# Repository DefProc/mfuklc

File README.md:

> Although the nerf range project was successful, it turned out that there was little interest in the competative building portion of this project. On the upside, the range had 5 installs during 2015, with hundreds of excited players during that time. 

> So although the MFUKLC project (it's a *terrible* acronym) has now reached it's conclusion, the same technology (with upgrades like full colour, animated, LED targets) lives on as [Made Invaders](https://github.com/DoESLiverpool/made-invaders).

> DefProc, 2016

# MFUKLC - Lasercut Challenge 
Your challenge, should you choose to accept it, is to build a device that can propel small light weight projectiles against a target. 

Round 1: MakerFaire UK 2015 (25-26 April Newcastle) [MakerFaire UK](http://www.makerfaireuk.com/). 

Round 2: MakeFest Liverpool 2015 (27th June, Central Library, Liverpool) [LpoolMakeFest](https://lpoolmakefest.wordpress.com).

Round 3: MakeFest Manchester 2015 (8–9th August, MOSI, Manchester) [MakeFest](http://www.mosi.org.uk/whats-on/makefest.aspx).

Round 4: Oggcamp '16

Take a look at the [rules](https://github.com/DefProc/mfuklc/tree/master/rules) to find out what you need to do. You can be a part of this challenge, either by entering at an event where the target will be, or by running your own event wherever and whenever you choose.

**Entries are now open to participate at Maker Faire UK 2015**

If you'd like to participate or have additional questions contact [@defproc](https://twitter.com/defproc) or [@MFUKLC](https://twitter.com/MFUKLC). Along with coming to [Maker Faire UK](http://www.makerfaireuk.com) in April 2015, we will also ask for:	

* your twitter name so we can add you to the [list of participants](https://twitter.com/MFUKLC/entrants),
* your github account name so we can give you write access to this repository,
* an email address would be nice in case we need to make any notifications,
* you be enthusiastic and open about your entry!
	
If you'd like to follow each teams progress and enjoy the trash talking follow the hash tag [ #MFUKLC](https://twitter.com/search?q=%23MFUKLC&src=typd) "**M**ega **F**un **U**nited **K**ingdom **L**aser **C**hallenge" or follow the twitter account [@MFUKLC](https://twitter.com/MFUKLC) to see @replies for the challenge in your timeline.
	
*Although this activity is running at the Maker Faire UK event, it is in no way affiliated with either Maker Faire UK or Make Media. It's an event being run by exhibitors* at *Maker Faire UK.*
	
## Repository Structure
	
 * [entries/](https://github.com/DefProc/mfuklc/tree/master/entries)
	* /AAAA/	subdirectories per entrant with 4-letter, upercase name,
 * [range/](https://github.com/DefProc/mfuklc/tree/master/range)	files for the range that will be used to score the entries,
 * [resources/](https://github.com/DefProc/mfuklc/tree/master/resources)	links, descriptions and resources to help participants, 
 * [rules/](https://github.com/DefProc/mfuklc/tree/master/rules)	the rules,
 * [trophy/](https://github.com/DefProc/mfuklc/tree/master/trophy)	files for the trophy.
	
## Short Link

Short link to this repository.

[defproc.co.uk/MFUKLC](http://defproc.co.uk/MFUKLC)

[oom.lt/MFUKLC](http://oom.lt/MFUKLC)

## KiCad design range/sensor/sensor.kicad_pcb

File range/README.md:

# Range

## Target

## Score Board  
   
The scoreboard is made using seven segment displays by [Matthew Venn](https://github.com/mattvenn/big-led-driver)

Files: MFUKLC-scoreboard-working.cdr (all other formats are generated (will switch to SVG once base design work done))

## Todo
* Sound -- Do we want a speaker or something more ecletic (fog horn)
* Target -- How many, what size/s how to house/hang

## Modules

### Control Module (CM)

The main control module.  

#### Microcontroller Pins (Arduino Mega)
* DIGITAL 13 -- Start Button -- (pin 13 so can connect other pin to ground with standard 2 pin header)

#### Connectors
* (U1) USB Type B -- For Arduino Connection
* (DC1) 2.1mm DC Jack -- For Power (12 v) 
* (BM) -- Button Module -- 2.1mm DC Jack -- N/O Switch
* (TM) -- Time Module -- 8 pin 2.54mm Dupont style connector 
* (SM) -- Score Module -- 8 pin 2.54mm Dupont style connector
* (RM) A-D -- Target modules -- To be determined.  

### Parts
* BOLT-M6-X-12-01 (x32) -- M6 x 12 mm Bolt
* NUTT-M6-M-STAN-01 (x32) -- M6 Nut
* CM-01 (x1) -- Base Plate
* CM-02 (x2) -- Side Plate
* CM-02-C (x1) -- Side Plate (Connections) Score Board
* CM-02-B (x1) -- Side Plate (Connections) Arduino (NOT YET DESIGNED)
* CM-03 (x1) -- Top (to be cut from acrylic)
* OOBB-MP-BREB-05-03 (x2) -- Breadboard Mounting Plate (5x3)
* OOBB-MP-ARDM-07-03 (x1)Arduino Mega Mounting Plate (7x3)
* OOBB-MP-I01-08-03-02 (A-D) (x2) -- Mounting Plate 8 pin 2.54 mm Connector

### Time Module (TM)

A 3 digit display to show the 30 second countdown
#### Connectors
* Only one (OE,LE,CLK,SDI,12V,5V,gnd) (gnd black)

#### Parts
* BOLT-M6-X-12-01 (x20) -- M6 x 12 mm Bolt
* NUTT-M6-M-STAN-01 (x20) -- M6 Nut
* NHFF-M3-X-30-01 (x12) -- M3 x 30 mm Nylon Standoff (F-F)
* NSCR-M3-X-12-70 (x24) -- M3 x 12 mm Nylon Screw Cross Head
* Matrix Module (x3) -- [Matrix Module](https://github.com/mattvenn/big-led-driver) -- By Matt Venn
* TM-01 (x1) -- Back -- Back, holds the matrices, and connector block
* TM-02 (x2) -- Side (Long) -- Long side piece.
* TM-03 (x1) -- Side (Short) -- Short side.
* TM-03-C (x1) -- Side (Short, Connections) -- Short Side with connections.
* TM-04 (x1) -- Top -- Top (to be cut from smoked acrylic)
* OOBB-MP-I01-08-03-02 (A-D) (x1) -- Mounting Plate 8 pin 2.54 mm Connector

### Score Module (SM)
A  6 digit display for showing the runs score.

#### Connectors
*    

#### Parts
* BOLT-M6-X-12-01 (x28) -- M6 x 12 mm Bolt
* NUTT-M6-M-STAN-01 (x28) -- M6 Nut
* NHFF-M3-X-30-01 (x12) -- M3 x 30 mm Nylon Standoff (F-F)
* NSCR-M3-X-12-70 (x24) -- M3 x 12 mm Nylon Screw Cross Head
* Matrix Module (x3) -- [Matrix Module](https://github.com/mattvenn/big-led-driver) -- By Matt Venn
* SM-01 (x1) -- Back -- Back, holds the matrices, and connector block
* SM-02 (x2) -- Side (Long) -- Long side piece.
* SM-03 (x1) -- Side (Short) -- Short side.
* SM-03-C (x1) -- Side (Short, Connections) -- Short Side with connections.
* SM-04 (x1) -- Top -- Top (to be cut from smoked acrylic)
* OOBB-MP-I01-08-03-02 (A-D) (x1) -- Mounting Plate 8 pin 2.54 mm Connector

### Target Module (RM) (x6) 

The targets

#### Connectors
* Only one 2.1mm barrel jack, center signal, outer gnd.

#### Parts
* BOLT-M6-X-12-01 (x8) -- M6 x 12 mm Bolt
* NUTT-M6-M-STAN-01 (x8) -- M6 Nut
* RM-01 (x1) -- Base -- The base that holds the PCB glued in place.
* RM-02 (x3) -- Side -- The side
* RM-02-C (x1) -- Side (Connections) -- The side with a hole for a 2.1mm barrel jack
* RM-03-2K (x1) -- Top (2000) -- The top (this one for 2000 points)

### Button Module (BM)

A 100 mm button to start the timing

#### Connectors
* Only one two pin button close (NO), 2.1mm DC jack.

#### Parts
* BOLT-M6-X-12-01 (x24) -- M6 x 12 mm Bolt
* NUTT-M6-M-STAN-01 (x24) -- M6 Nut
* ABUT-100-R-STAN-01 (x1) -- 100 mm Red Arcade Button
* DCJP-21D-X-08PM-01 (x1) -- 2.1 mm Panel Mount (8mm) DC Jack
* CRFM-48D-R-STAN-01 (x2) -- 4.8 mm Red Female Crimp Connector
* BM-01 (x1) -- Top -- Has a hole for a 100 mm button, is  173 mm x 173 mm (9x9 OOBB)
* BM-02 (x3) -- Side -- Side Panel 
* BM-02-C (x1) -- Side (Connections) -- Side Panel with conenctions
* BM-03 (x1) -- Bottom -- Bottom Panel173 mm x 173 mm (9x9 OOBB)
* BM-04 (x2) -- Base -- A base for the box to sit on, has holes to screw down or glue stars to glue.

## Bin Lid

Transporting amunition is an issue. We use a rubbish bin with a custom lid.

## Stencil

Branding is always important. To aid in this we have an A4 #MFUKLC stencil

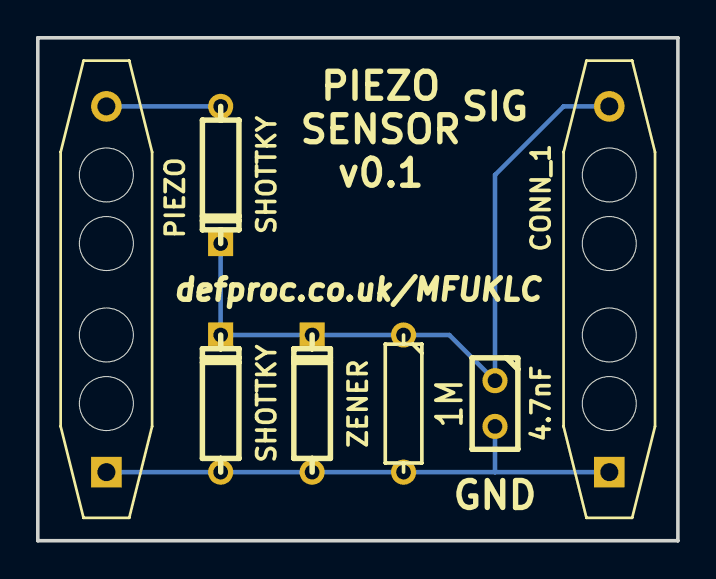
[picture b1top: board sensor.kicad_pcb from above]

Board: 2 copper layers, 35.6 x 27.9 mm, 7 parts (0 on the bottom side), 3 nets.

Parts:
4.7nF: 4.7nF; C1
CONN_1: CONN_2; PZ1
PIEZO: PIEZO; PZ1
R1: 1M; R3
SHOTTKY: SHOTTKY DIODE SR1100; D3
SHOTTKY#2: SHOTTKY DIODE SR1100; D3
ZENER: ZENER DIODE 1N751A; D3

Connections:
GND: 4.7nF.2, CONN_1.2, PIEZO.2, R1.2, SHOTTKY.1, ZENER.1
unnamed: PIEZO.1, SHOTTKY#2.1
SIGNAL: 4.7nF.1, CONN_1.1, R1.1, SHOTTKY.2, SHOTTKY#2.2, ZENER.2

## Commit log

2015-01-27 Initial Workings
    -File structure added
    -Main readme filled in
    -Added trophy files
    -Added Oomlout's entry file (no working yet)
2015-01-27 Added README.md's to empty folders
2015-01-27 revised licence file to allow individual entries their own terms
2015-01-27 moved the rules draft from google docs into markdown here
2015-01-27 Updated shortlink to point to this repository.
2015-01-27 Changed shortlink.
2015-01-28 Oomlout's Initial Workings
    Oomlout Changes
    - Pieces to cut to prototype a launcher
    - Notes added to readme (Inspiration, Proto Parts, Files Explained)
    - Generated file formats made
    Main Body Changes
    - Added link to hash tag to main readme.
2015-01-28 Fixed Markdown Formatting
2015-01-28 Re-Fixed MarkDown Formatting
2015-01-29 Some Design Working, Trophy Updating
2015-01-29 Fixing Image Link
2015-01-29 Changed Acronym to Mega Fun
2015-01-30 Added HobbyKing Second Round Sample Details
2015-01-30 Updated Design, and Trophy
2015-02-01 make sure it's clear that the MFUKLC project is not affiliated with the event
2015-02-02 Prototype one details.
2015-02-02 renamed root dirs to lowercase (because convention and cli typing!)
2015-02-02 removed backup file — because git!
2015-02-02 Doing a lot of housekeeping and not much designing #justSaying
2015-02-02 Launcher Refactoring
2015-02-02 added gitignore for kicad files
2015-02-02 first pass at the sensor schematic
2015-02-02 at least someone's doing the tidying up!
2015-02-03 updates to resources for ball and dart pricing
2015-02-03 Slight Change to design
2015-02-03 Design Changing
2015-02-04 Added Speed spreadsheet, and more HobbyKing Stuff
2015-02-05 Fixed folder capitalization issue.
2015-02-05 Motor mounts for new design. Updated Design notes.
2015-02-05 Updated Design Notes
2015-02-05 Fixed Markup, Added image resolutions
2015-02-05 Tidied up MarkUp
2015-02-05 Formatted README Entry page.
2015-02-05 Final Current Readme Updates
2015-02-05 Added Youtube video for motor balancing.
2015-02-05 Fixed Up Pieces for Prototype 3
2015-02-05 Added Scoreboard Working, generated images.
2015-02-05 Fixed Scoreboard Image
2015-02-05 Changed Scoreboard Image Size
2015-02-05 Generated formats for viewing/sharing.
2015-02-06 Added T-Joint to Vacuum Design
2015-02-06 moved to entries — I think this is where you meant
2015-02-06 added @MFUKLC twitter account and corrected folder names
2015-02-06 Added version one files and images
    Also contains failure and improvement write up
2015-02-06 Improvements list added for V1
2015-02-06 housekeeping: moved PIMO to entries/
2015-02-06 added some design notes to the DEFP entry
2015-02-06 confirmation that we'll be at maker faire and the call for entries
2015-02-07 Moved and updated Vacuum Testing
2015-02-07 Split Entries OOML & OOMV
2015-02-07 Added Directory to Entries Readme
2015-02-07 Fixed Markdown issues (discovered preview mode so hopefully fewer edits from me)
2015-02-07 Fixed Pimoroni Web Address
2015-02-07 Generated Files
2015-02-07 Moved Resources from ammunition.mkdn to README.md (added OOML sources)
2015-02-07 Fixed List Format
2015-02-07 Added additional amazon source
2015-02-07 Worked on designs.
2015-02-07 Added todo notes. Drew new vacuum nozzle
2015-02-08 Generated Formats.
2015-02-08 had a go at creating a piezo board and gerbers
2015-02-10 Updated Design, Removed video files from
2015-02-10 Updated Design documenting
2015-02-10 Fixed current entry image.
2015-02-10 updated the main README to include links
2015-02-10 added svg ammunition templates to resources
2015-02-10 Updated design (worked on ball chain and ball feeder)
2015-02-11 new defproc.co.uk/MFUKLC short link
2015-02-12 Worked on design a bit.
2015-02-12 Removed old files from git repo.
2015-02-12 Worked on design
2015-02-17 Version 2 first commit
2015-02-20 Updated Design.
    Added Prototype 4 to README
    Added Additional Hobby King test Components
    Added Images of P4 and control.
2015-02-25 Updated Entry Details.
2015-02-25 Worked on scoreboard.
2015-02-26 Some scoreboard changes.
2015-02-26 Added Score Board Images
2015-02-26 Added Resolutions
2015-02-26 Updated Scoreboard Readme With Images
2015-02-27 Added Score Module
2015-03-04 Started working on cleaning up.
2015-03-05 Worked on drive wheel.
2015-03-08 Updated Scoreboard
2015-03-09 added cardboard box range components
2015-03-09 Worked on Making Design Cleaner
2015-03-15 revised sensor board, and removed previous gerbers
2015-03-15 added rev.2 gerbers
2015-03-24 added code for serial controlled, 30 second, 8 segment LED countdown display
2015-03-24 new, basic piezo sensor tester using INT0 and LED_BUILTIN
2015-03-26 Changed to RJ45 panel holes.
2015-03-27 Added details about prototype 5.
2015-03-27 Slight README Change
2015-04-01 added display (scoreboard) function to the coutdown timer
2015-04-01 new dates, round 2: LpoolMakeFest, applied for Manchester MakeFest
2015-04-01 Updated Scoreboard and timer for integrated Arduino.
2015-04-01 Added DC jack hole to scoreboard.
2015-04-02 piezo hit counter to scoreboard
2015-04-02 confirmed attendence at Manchester MakeFest
2015-04-16 number display is now a long
2015-04-17 analog based piezo checking, along with 1ms timer interrupt
2015-04-18 Worked on design.
    Fixed some small issues.
    Worked heavily on feeder.
    Made box for electronics.
2015-04-20 Added bin lid for ping pong ball transportation, and stencil for branding.
2015-04-20 Worked on design.
    Added carrier.
    Added holder for turret.
    Added new magazine style.
2015-04-21 Minor tweaks.
2015-04-21 target module code
2015-04-21 control module draft (untested)
2015-04-21 updated the svg, eps and dxf files to match commit a48bc261d
2015-04-21 svgs of the vinyls for the face of the target boxes
2015-04-21 svg versions of each electronics enclosures
2015-04-22 added the 16 sensor socket holes to the target module
2015-04-22 corrections to target module svg for easier laser cutting
2015-04-23 vinyl stickers for the target boxes
2015-04-23 datafile should store target hits indexed to 1
2015-04-23 revised all the boxes and cases to match the layout that's been cut for MFUK'15
2015-04-23 added debug flag to stop reporting erronious scores
2015-04-29 control moudule code, as at MFUK15
2015-04-29 Just Add Sharks' files in ADSH
2015-05-18 raw scores included from MFUK2015
2015-06-09 added FACT scores
2015-06-12 Added instructions, code, etc. for the Registration Station
2015-06-19 added negative number support to the number display
2015-06-22 changed score to signed long #2
2015-06-22 removed the delay at zero for player scoring
2015-06-22 clear scores in serial bufffer at reset (untested) #1
2015-06-26 fixed missing digit on D0
2015-06-28 EOD Liverpool MakeFest hotfixes and new sound code
2015-10-31 fixed unsigned long (target module) → to long (control module) bug
2015-11-01 Removed incorrect specifier initialising current_score
2016-04-13 end of project explaination
